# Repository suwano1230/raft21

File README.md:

# raft21（ソクタイプ型のDIYキーボード）

## 概要
Stenturaプロトコル互換で動くソクタイプ型のDIYキーボードです。  
ソクタイプは21キーで、キーの配置やキーキャップのサイズ、表面のくぼみ、高低差があるなどの特徴があります。  
Ploverでの動作は確認できましたが、Stenturaプロトコルと同一のものではありません。  
実機などから情報を得てStenturaプロトコルを再現したということはありません。  
また、キーキャップのサイズなどに関して、ソクタイプの厳密な再現とは言えない可能性があります。  
## PCB基盤
KiCadを使用して作成。MCUはRP2040（Raspberry Pi Pico）を使用します。  
MCUはピンヘッダを使わない直接はんだ付け、基盤の厚さは1.6mm厚の前提でケースを設計しています。
## スイッチプレート
KiCadを使用して作成。基盤を発注するのと同様に発注します。1.6mm厚の前提でケースは作成しています。
## キーキャップ
ソクタイプ型のキーキャップを再現するために3Dプリンターで作成します。
## ケース
3Dプリンターで作成します。`bottom-case.stl`
## 製作に必要なもの（上記以外）
| 名称　　　　  | 個数　　　　  | 備考   　　　　 
|:------------:|:------------:|:------------:|
| Raspberry Pi Pico  |      1      |     Pico 2 ではない   |
| PCBソケット  |     21     |スイッチを直接はんだ付けするなら不要|
| Cherry MX互換スイッチ  |     21     |     赤軸静音推奨　　　　     |
| プレートマウントスタビライザー 2U   |      4      |     MX用 |
| M2 6mm ねじ       |     7     |     底用ねじ     |
| M2 4mm ねじ       |     7     |     天用ねじ     |
| M2 8mm スペーサー  |     7     |    外径4.0mm以下   |
| Micro USB ケーブル  |     1     |   データ転送対応のもの |
| ゴム足 10mm  |     4     |     　高さ任意　　　     |

※PCBソケット（使用しないならスイッチ）と Raspberry Pi PicoをPCB基盤にはんだ付けする必要があります。

※両手の人差し指側につけるスタビライザーは、接触する箇所があります。  
　適宜ニッパー等でカットし、接触しないようにする必要があります。

※キースイッチとばねをルブ（潤滑）するなら、キースイッチ用とばね用の潤滑剤が必要です。

※キースイッチのばねを取り替えるなら、それも必要です。  
　赤軸静音使用時、20g 14mmは戻る力がぎりぎり足りませんでした。  
　19g 22mmはぎりぎりセーフでした。長期の使用に耐えるかは不明です。

## uf2ファイル
BOOTSELボタンを押しながらUSBケーブルを接続し、Raspberry Pi Picoを書き込みモードで立ち上げ、そのフォルダ内にuf2ファイルをコピーすることで書き込みできます。

## 参考
- [Plover](https://github.com/opensteno/plover)  
- [電子速記研究会 （はやとくんの会）](https://www.hayatokun.com/)
- [電子速記はやとくん](https://www.youtube.com/@%E9%9B%BB%E5%AD%90%E9%80%9F%E8%A8%98%E3%81%AF%E3%82%84%E3%81%A8%E3%81%8F%E3%82%93/shorts)

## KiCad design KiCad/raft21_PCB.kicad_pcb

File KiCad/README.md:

## PCB基盤
`raft21_PCB.kicad_pcb`
## 回路図
ほかの設計を変更するとしても、ピンとスイッチの対応をこのファイルのとおりにすれば、uf2ファイルの書き込み後、期待どおりの動作をするはずです。`raft21_PCB.kicad_sch`
## スイッチプレート
`raft21_switchplate.kicad_pcb`
## PCB基盤のガーバーファイル
PCB基盤の発注時に必要なファイル一式。`raft21-PCB-gerber.zip` 
## スイッチプレートのガーバーファイル
スイッチプレートの発注時に必要なファイル一式。`raft21-switchplate-gerber.zip`

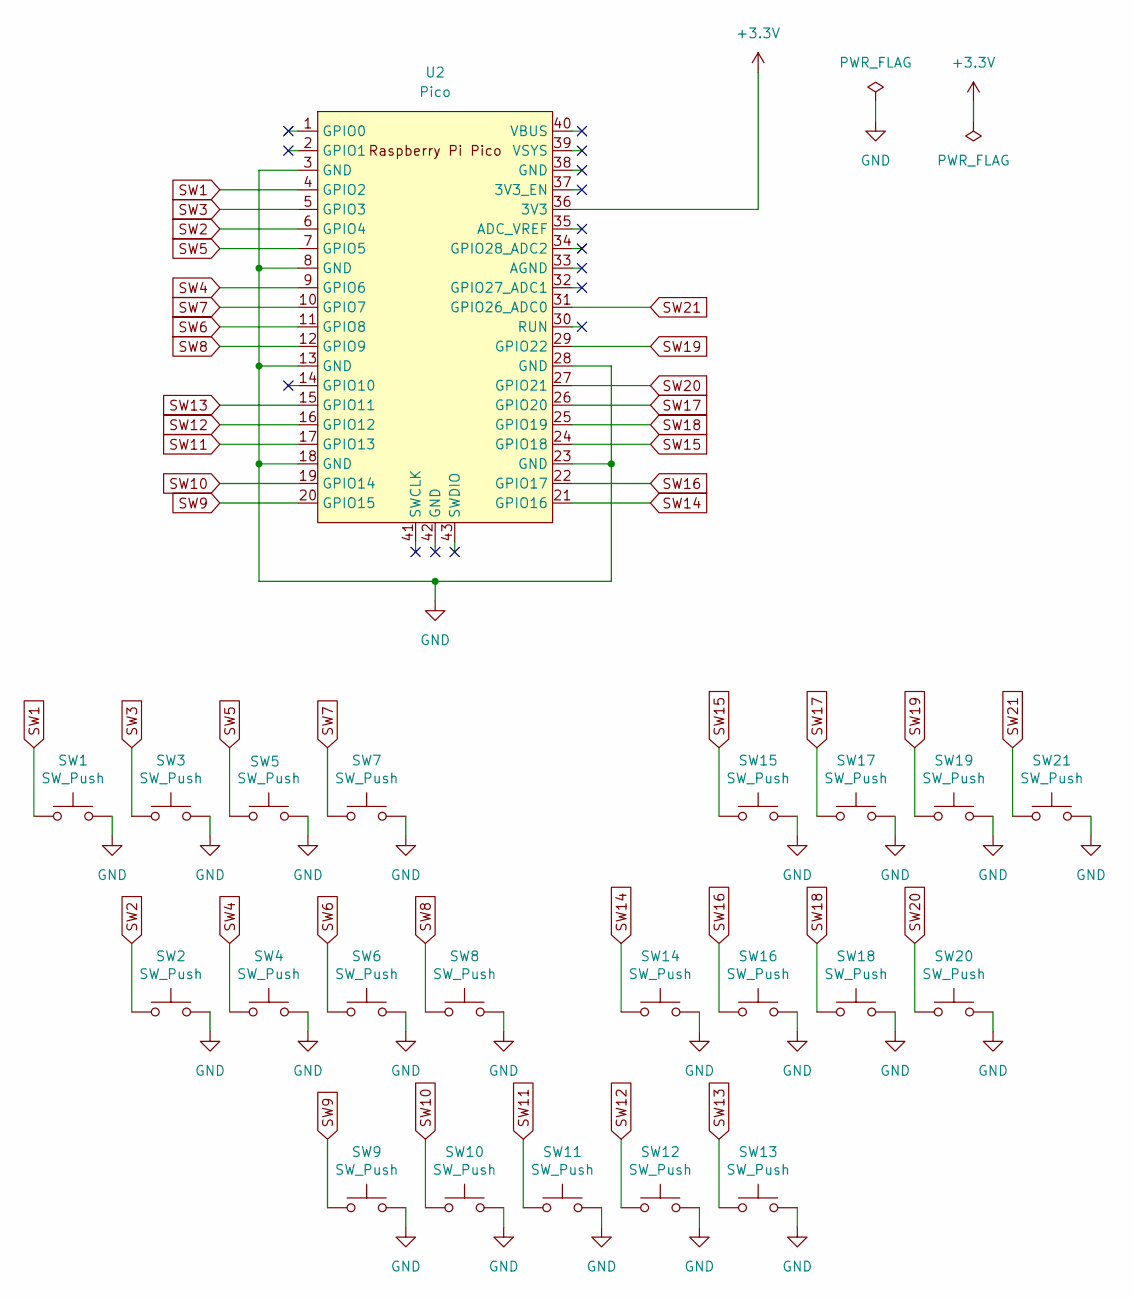
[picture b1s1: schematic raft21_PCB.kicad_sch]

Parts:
SW1, SW8, SW14, SW21: SW_Push; CherryMX_Hotswap_2.25u
SW2, SW3, SW4, SW5, SW6, SW7, SW9, SW10, SW11, SW12, SW13, SW15, SW16, SW17, SW18, SW19, SW20: SW_Push; CherryMX_Hotswap_1.25u
U2: Pico; RPi_Pico_SMD_TH

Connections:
+3.3V: U2.36 (3V3)
GND: SW1.2, SW2.2, SW3.2, SW4.2, SW5.2, SW6.2, SW7.2, SW8.2, SW9.2, SW10.2, SW11.2, SW12.2, SW13.2, SW14.2, SW15.2, SW16.2, SW17.2, SW18.2, SW19.2, SW20.2, SW21.2, U2.3 (GND), U2.8 (GND), U2.13 (GND), U2.18 (GND), U2.23 (GND), U2.28 (GND)
SW1: SW1.1, U2.4 (GPIO2)
SW2: SW2.1, U2.6 (GPIO4)
SW3: SW3.1, U2.5 (GPIO3)
SW4: SW4.1, U2.9 (GPIO6)
SW5: SW5.1, U2.7 (GPIO5)
SW6: SW6.1, U2.11 (GPIO8)
SW7: SW7.1, U2.10 (GPIO7)
SW8: SW8.1, U2.12 (GPIO9)
SW9: SW9.1, U2.20 (GPIO15)
SW10: SW10.1, U2.19 (GPIO14)
SW11: SW11.1, U2.17 (GPIO13)
SW12: SW12.1, U2.16 (GPIO12)
SW13: SW13.1, U2.15 (GPIO11)
SW14: SW14.1, U2.21 (GPIO16)
SW15: SW15.1, U2.24 (GPIO18)
SW16: SW16.1, U2.22 (GPIO17)
SW17: SW17.1, U2.26 (GPIO20)
SW18: SW18.1, U2.25 (GPIO19)
SW19: SW19.1, U2.29 (GPIO22)
SW20: SW20.1, U2.27 (GPIO21)
SW21: SW21.1, U2.31 (GPIO26_ADC0)

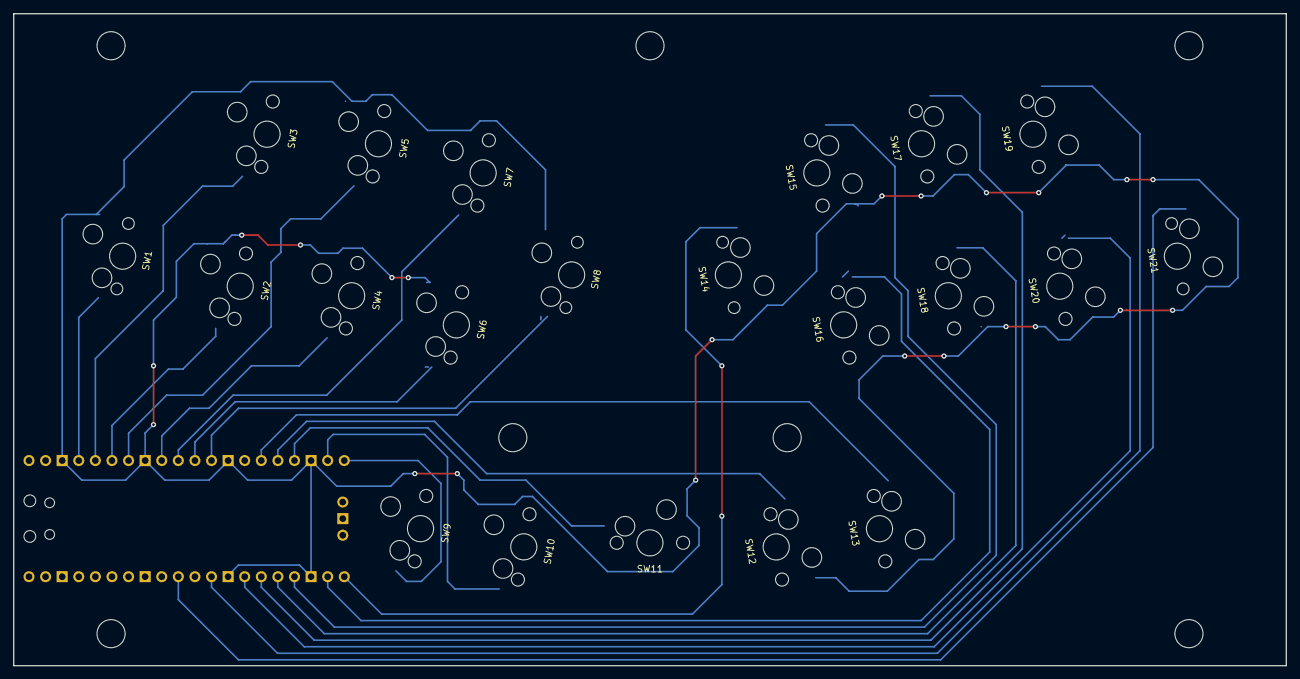
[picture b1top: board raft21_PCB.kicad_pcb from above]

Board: 2 copper layers, 194.8 x 99.8 mm, 22 parts (1 on the bottom side), 22 nets.

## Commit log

2026-04-26 README.md を作成
2026-04-26 README.md を更新
